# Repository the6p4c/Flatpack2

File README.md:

# Flatpack2
Software, hardware and protocol information for the Eltek Flatpack2.

Provided is [a simple voltage changing Arduino sketch](Arduino/fp2_set_voltage/).

Check [Protocol.md](https://github.com/The6P4C/Flatpack2/blob/master/Protocol.md) for information about the CAN bus protocol used by the Flatpack2.

# Transceiver + Breakout Board

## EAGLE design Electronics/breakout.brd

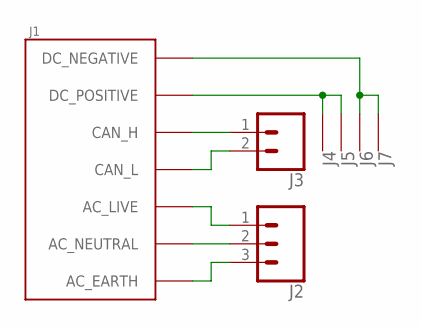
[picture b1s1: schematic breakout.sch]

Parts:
J1: FLATPACK2_CON
J2: WEIDMULLER_PM_508
J3: CONN_021X02_NO_SILK; 1X02_NO_SILK
J4, J5, J6, J7: FLATPACK2_DC_LUG

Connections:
unnamed: J1.CAN_H_TOP (CAN_H), J3.1
unnamed: J1.CAN_L_TOP (CAN_L), J3.2
unnamed: J1.AC_LIVE_BOTTOM (AC_LIVE), J1.AC_LIVE_TOP (AC_LIVE), J2.1
unnamed: J1.AC_NEUTRAL_BOTTOM (AC_NEUTRAL), J1.AC_NEUTRAL_TOP (AC_NEUTRAL), J2.2
unnamed: J1.DC_POSITIVE_BOTTOM (DC_POSITIVE), J1.DC_POSITIVE_TOP (DC_POSITIVE), J4.P$1, J5.P$1
unnamed: J1.AC_EARTH, J2.3
unnamed: J1.DC_NEGATIVE_BOTTOM (DC_NEGATIVE), J1.DC_NEGATIVE_TOP (DC_NEGATIVE), J6.P$1, J7.P$1

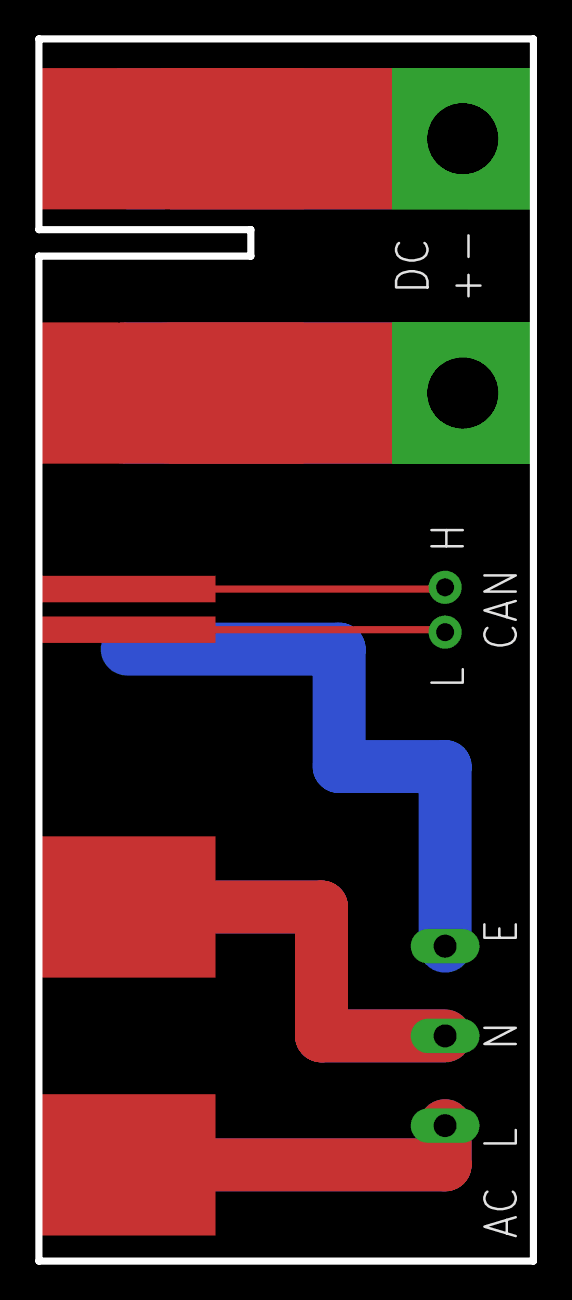
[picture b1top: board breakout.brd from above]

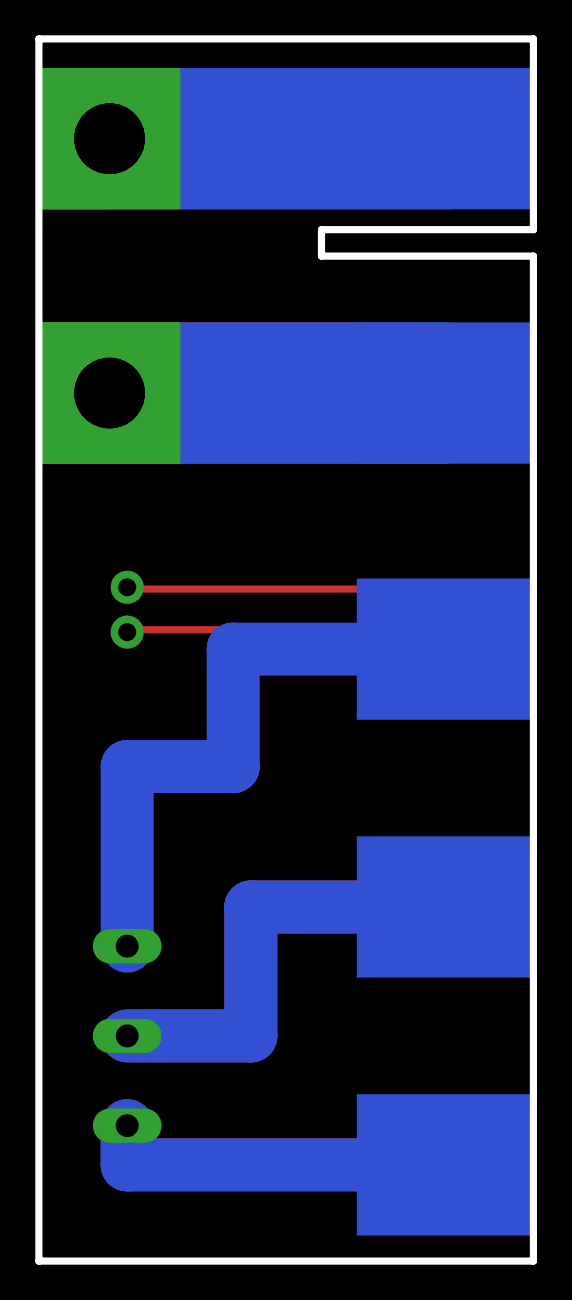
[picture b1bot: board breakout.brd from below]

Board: 2 copper layers, 28.0 x 69.2 mm, 7 parts (2 on the bottom side), 7 nets.

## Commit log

2017-02-11 Correct edge connector dimensions and show both sides in DXF
2017-02-11 Mirror bottom in edge connector CAD model
2017-02-12 Formatting changes in protocol description
2017-02-12 Add hardware information and formatting improvements to Protocol.md
2017-02-12 Add more info to Protocol.md
2017-02-12 Remove old Arduino code
2017-02-14 Lots of changes; final board revision
2017-02-14 Fix typo in Protocol.md
2017-03-19 Final revision of Flatpack breakout PCB
2017-03-26 Add voltage setting sketch
2017-04-08 Reformat protocol document
2017-04-08 Complete replacement of most files.
2017-04-08 Rename from eltek to fp2
2017-04-08 Add CAN bus transceiver sketch
2017-04-08 Print ASCII in test sketch
2017-04-08 Reshuffle and rename some messages in protocol
2017-06-18 Fix merge conflict
2017-09-18 Update for schematic conventions
2019-02-22 Add images of breakout board and transceiver schematic
2019-02-22 Add some documentation for the fp2_set_voltage sketch

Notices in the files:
parts and their libraries:
SparkFun-Connectors: Licensing: Creative Commons ShareAlike 4.0 International - https://creativecommons.org/licenses/by-sa/4.0
